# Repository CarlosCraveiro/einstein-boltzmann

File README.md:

# The Einstein-Boltzmann Board

## Project's Intent
Measure the Boltzmann constant through the analysis of the thermal noise of a resistor.

## Disclaimer
This Board was intended to be used with the Guide of the [5-th EPO (2017)](https://github.com/CarlosCraveiro/einstein-boltzmann/tree/main/docs).

So the schematic ideia is not mine, I just adapt and documented it so I could manufacture the board.

The DRC Custom Rules used on this project came from a gist made by [darkxst](https://gist.github.com/darkxst), Gist name: `rules.txt`.

## Project's Dependencies

- KiCAD version 7.0
- KiCAD Addon [kicad-action-scripts](https://github.com/jsreynaud/kicad-action-scripts) (via stitching)

If you use `nix`, to have access to **KiCAD 7.0**, on the project's directory type:

```shell
nix --experimental-features 'nix-command flakes'
nix develop -c $SHELL
```

## Preview Images

### Main Board

### Modules

## Real Photos

## TO DO...
- [ ]  Finish soldering the components and modules
- [ ]  Create a Wiki for the project
- [ ]  Measure the Boltzmann constant and publish the results on the project's Wiki
- [ ]  Finish the plate support base (using FreeCAD)
- [ ]  Write a theoretical introduction about the phenomenon on the project's Wiki

*Observation*: I intend to continue working on the project, I just need time.

## Additional information:

I talked about the project at the [FOSFORUMS 2024](https://www.fosforums.org/home) event. The presentation were in English and both the slides and the link for the presentation recording could be access [here](https://github.com/CarlosCraveiro/FOSFORUMS_2024).

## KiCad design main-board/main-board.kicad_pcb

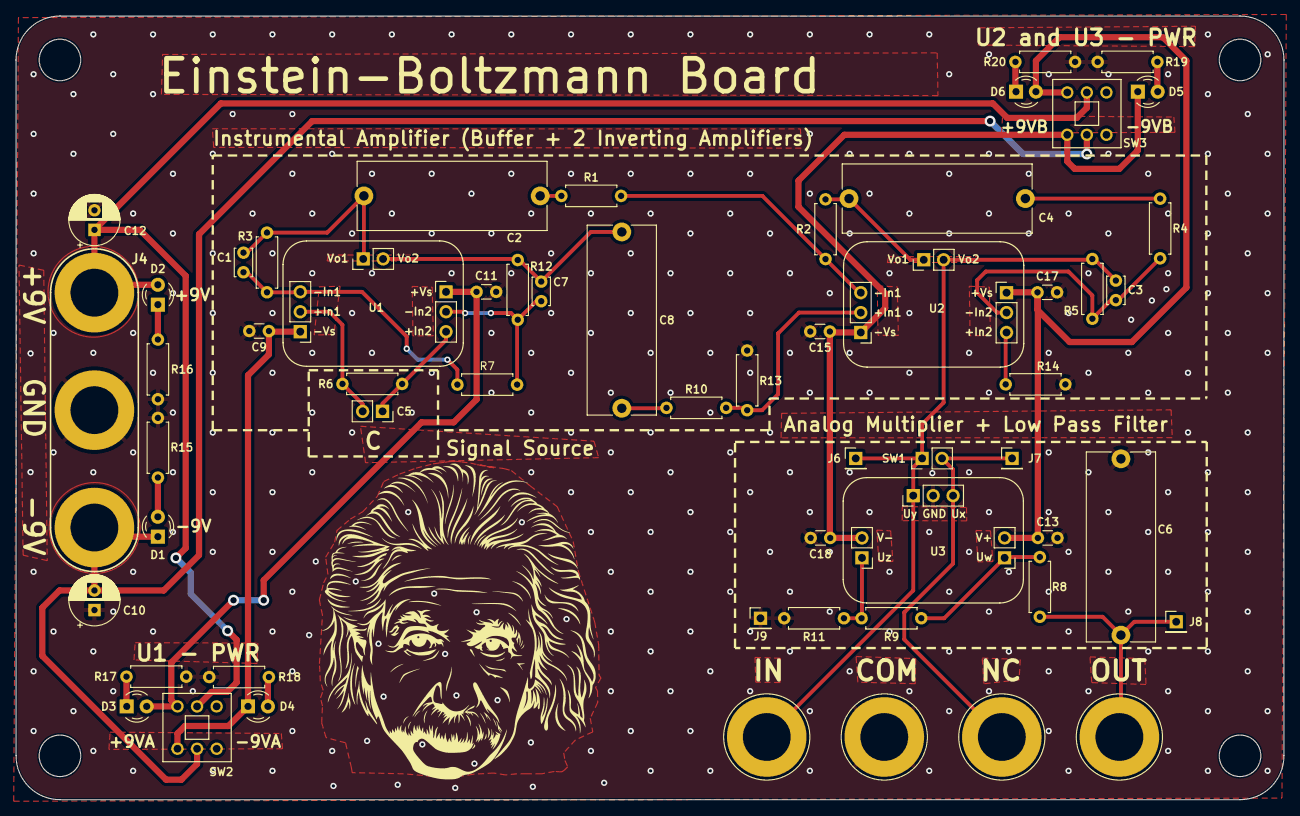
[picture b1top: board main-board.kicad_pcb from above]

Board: 2 copper layers, 161.8 x 100.0 mm, 61 parts (0 on the bottom side), 32 nets.

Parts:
C1, C3, C7: 10p; C_Disc_D3.4mm_W2.1mm_P2.50mm
C2, C4, C6, C8: 10u; C_Rect_L24.0mm_W8.6mm_P22.50mm_MKT
C5: c=?; CapacitorSocket
C9, C11, C13, C15, C17, C18: 0.1u; C_Disc_D3.0mm_W1.6mm_P2.50mm
C10, C12: 10u; CP_Radial_D6.3mm_P2.50mm
D1, D2, D3, D4, D5, D6: LED; LED_D3.0mm
H1, H2, H3, H4: MountingHole; MountingHole_5.3mm_M5
J1: INPUT; Banana_Jack_1Pin
J2: NC1; Banana_Jack_1Pin
J3: OUTPUT; Banana_Jack_1Pin
J4: Conn_01x03_Pin; Banana_Jack_3Pin
J5: COM; Banana_Jack_1Pin
J6: INPUT_DEBUG; PinHeader_1x01_P2.54mm_Vertical
J7: NC__DEBUG; PinHeader_1x01_P2.54mm_Vertical
J8: OUTPUT_DEBUG; PinHeader_1x01_P2.54mm_Vertical
J9: COM_DEBUG; PinHeader_1x01_P2.54mm_Vertical
R1, R4, R10, R14: 100; R_Axial_DIN0207_L6.3mm_D2.5mm_P7.62mm_Horizontal
R2, R5, R13: 10k; R_Axial_DIN0207_L6.3mm_D2.5mm_P7.62mm_Horizontal
R3, R12: 1k; R_Axial_DIN0207_L6.3mm_D2.5mm_P7.62mm_Horizontal
R6: 510; R_Axial_DIN0207_L6.3mm_D2.5mm_P7.62mm_Horizontal
R7: 20; R_Axial_DIN0207_L6.3mm_D2.5mm_P7.62mm_Horizontal
R8: 1.5M; R_Axial_DIN0207_L6.3mm_D2.5mm_P7.62mm_Horizontal
R9, R15, R16, R17, R18, R19, R20: 2k; R_Axial_DIN0207_L6.3mm_D2.5mm_P7.62mm_Horizontal
R11: 18k; R_Axial_DIN0207_L6.3mm_D2.5mm_P7.62mm_Horizontal
SW1: SW_SPST; Switch
SW2: Power Switch A; SW_Push_2P2T_Toggle_CK_PSW-8,0R
SW3: Power Switch B; SW_Push_2P2T_Toggle_CK_PSW-8,0R
U1, U2: ADA4898-2
U3: AD633ANZ; AD633

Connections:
+9V: C12.1, D2.2 (A), J4.1, SW2.2 (B), SW3.2 (B)
+9VA: C11.1, D3.2 (A), SW2.1 (A), U1.6 (+Vs)
+9VB: C13.1, C17.1, D6.2 (A), SW3.1 (A), U2.6 (+Vs), U3.6 (V+)
-9V: C10.2, D1.1 (K), J4.3, SW2.5 (B), SW3.5 (B)
-9VA: C9.1, D4.1 (K), SW2.4 (A), U1.1 (-Vs)
-9VB: C15.1, C18.1, D5.1 (K), SW3.4 (A), U2.1 (-Vs), U3.2 (V-)
/led_+9V: D2.1 (K), R16.1
/led_+9VA: D3.1 (K), R17.1
/led_+9VB: D6.1 (K), R20.1
/led_-9V: D1.2 (A), R15.1
/led_-9VA: D4.2 (A), R18.1
/led_-9VB: D5.2 (A), R19.1
/w1: C1.1, R3.1, R7.1, U1.3 (-In1)
/w2: C7.1, R7.2, R12.2, U1.7 (-In2)
/w3: C1.2, C2.1, R3.2, U1.4 (Vo1)
/w4: C7.2, C8.1, R12.1, U1.5 (Vo2)
/w5: C2.2, R1.1
/w6: C8.2, R10.1
/w7: R1.2, R2.1, U2.3 (-In1)
/w8: R10.2, R13.2, U2.2 (+In1)
/w9: R14.2, U2.8 (+In2)
/w10: C4.1, R2.2, U2.4 (Vo1)
/w11: C4.2, R4.1
/w12: C3.1, R4.2, R5.1, U2.7 (-In2)
/w13: R8.1, R9.1, U3.7 (Uw)
/w14: R9.2, R11.1, U3.1 (Uz)
/w_input: C3.2, J1.1, J6.1, R5.2, SW1.1 (A), U2.5 (Vo2), U3.3 (Uy)
/w_nc: J2.1, J7.1, SW1.2 (B), U3.5 (Ux)
/w_out: C6.1, J3.1, J8.1, R8.2
/w_signal+: C5.2, R6.1, U1.2 (+In1)
/w_signal-: C5.1, R6.2, U1.8 (+In2)
GND: C6.2, C9.2, C10.1, C11.2, C12.2, C13.2, C15.2, C17.2, C18.2, J4.2, J5.1, J9.1, R11.2, R13.1, R14.1, R15.2, R16.2, R17.2, R18.2, R19.2, R20.2, U3.4 (GND)

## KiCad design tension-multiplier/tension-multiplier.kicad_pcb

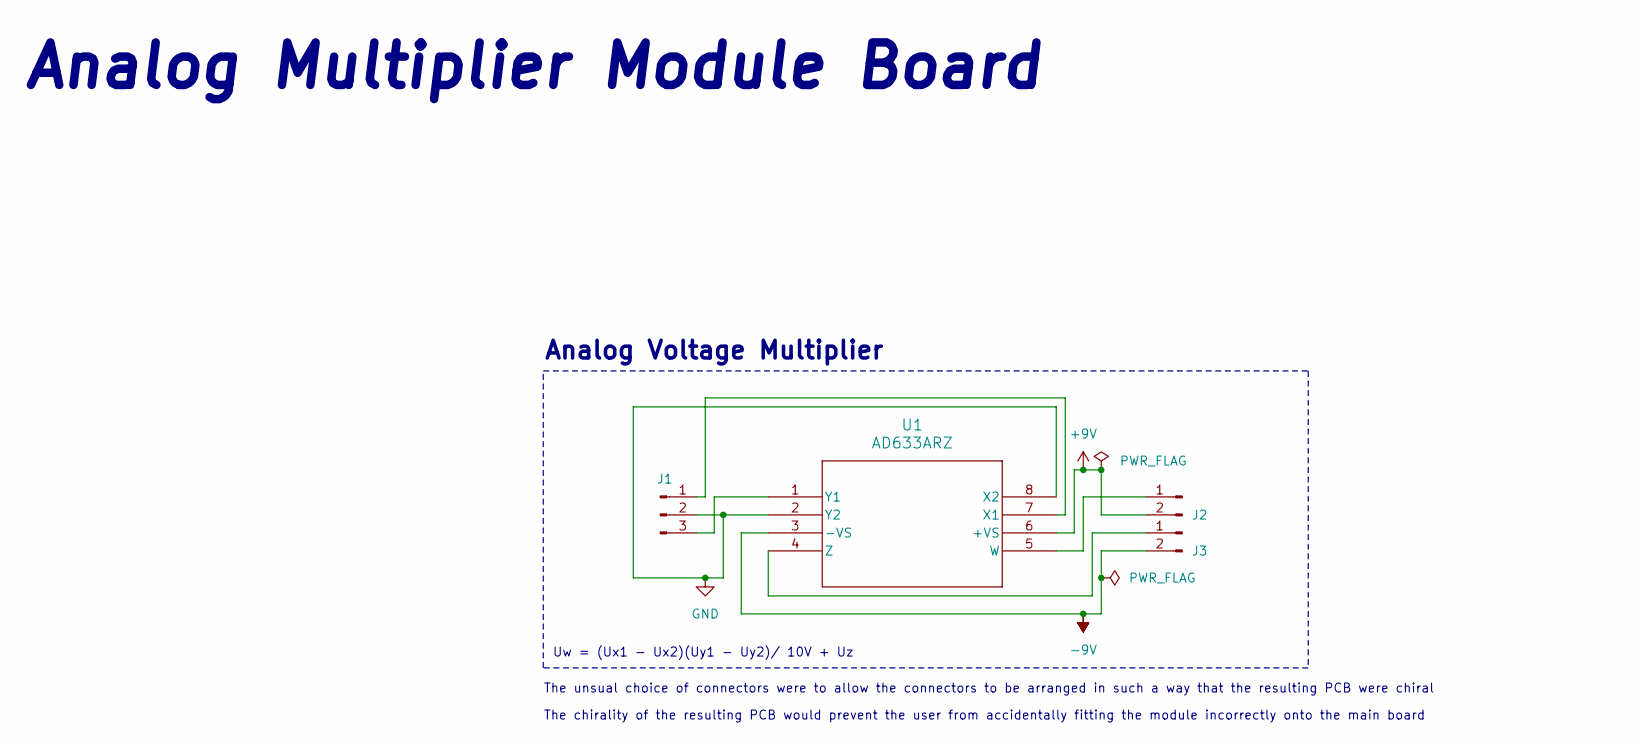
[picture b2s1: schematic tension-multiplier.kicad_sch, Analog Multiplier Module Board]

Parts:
J1: Conn_01x03_Pin; PinHeader_1x03_P2.54mm_Vertical
J2, J3: Conn_01x02_Pin; PinHeader_1x02_P2.54mm_Vertical
U1: AD633ARZ; R_8_ADI

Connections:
+9V: J2.2, U1.6 (+VS)
-9V: J3.2, U1.3 (-VS)
GND: J1.2, U1.2 (Y2), U1.8 (X2)
unnamed: J1.1, U1.7 (X1)
unnamed: J1.3, U1.1 (Y1)
unnamed: J2.1, U1.5 (W)
unnamed: J3.1, U1.4 (Z)

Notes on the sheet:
The chirality of the resulting PCB would prevent the user from accidentally fitting the module incorrectly onto the main board
Analog Multiplier Module Board
Analog Voltage Multiplier
The unsual choice of connectors were to allow the connectors to be arranged in such a way that the resulting PCB were chiral
Uw = (Ux1 - Ux2)(Uy1 - Uy2)/ 10V + Uz

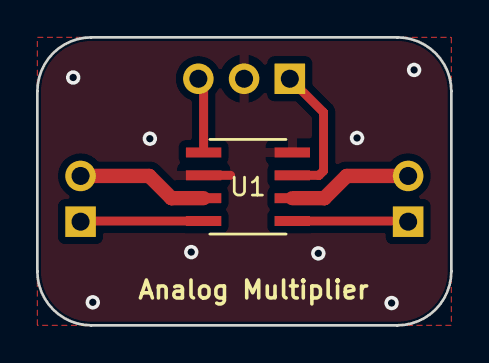
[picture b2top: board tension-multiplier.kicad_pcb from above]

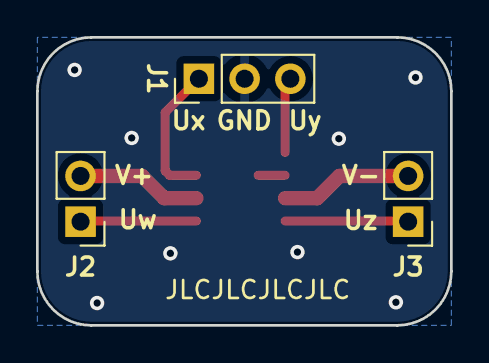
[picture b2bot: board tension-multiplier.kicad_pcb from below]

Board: 2 copper layers, 23.0 x 16.0 mm, 4 parts (3 on the bottom side), 7 nets.

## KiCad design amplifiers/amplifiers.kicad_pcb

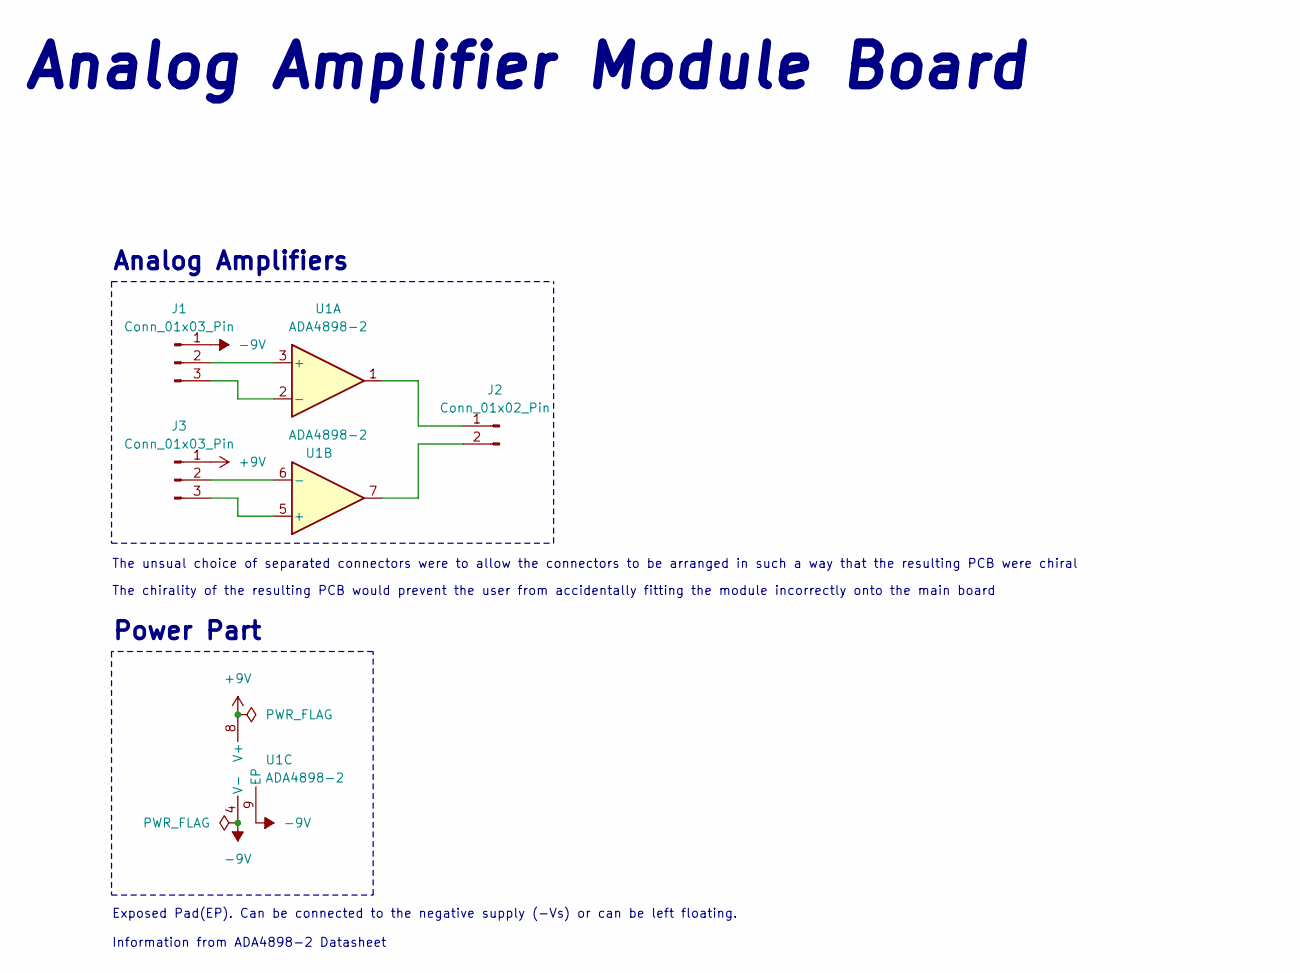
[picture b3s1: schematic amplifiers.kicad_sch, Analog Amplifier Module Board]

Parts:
J1, J3: Conn_01x03_Pin; PinHeader_1x03_P2.54mm_Vertical
J2: Conn_01x02_Pin; PinHeader_1x02_P2.54mm_Vertical
U1: ADA4898-2; SOIC-8-1EP_3.9x4.9mm_P1.27mm_EP2.41x3.81mm

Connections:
+9V: J3.1, U1.8 (V+)
-9V: J1.1, U1.4 (V-), U1.9 (EP)
unnamed: J1.2, U1.3 (+)
unnamed: J1.3, U1.2 (-)
unnamed: J2.1, U1.1
unnamed: J2.2, U1.7
unnamed: J3.2, U1.6 (-)
unnamed: J3.3, U1.5 (+)

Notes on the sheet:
Power Part
The unsual choice of separated connectors were to allow the connectors to be arranged in such a way that the resulting PCB were chiral
Exposed Pad(EP). Can be connected to the negative supply (−Vs) or can be left floating. Information from ADA4898-2 Datasheet
Analog Amplifier Module Board
Analog Amplifiers
The chirality of the resulting PCB would prevent the user from accidentally fitting the module incorrectly onto the main board

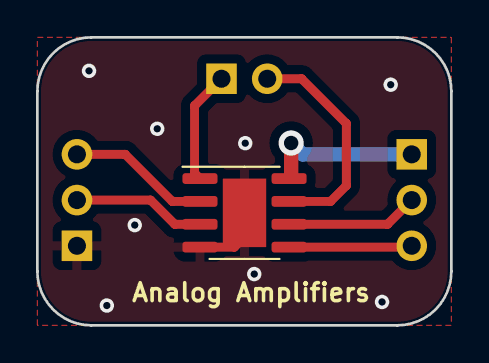
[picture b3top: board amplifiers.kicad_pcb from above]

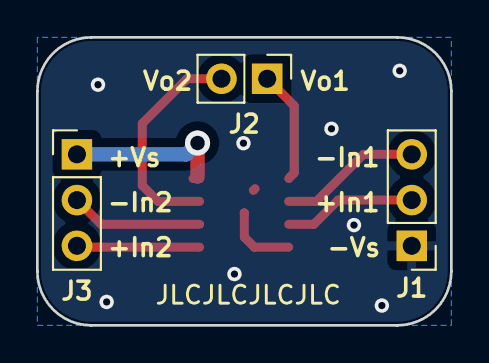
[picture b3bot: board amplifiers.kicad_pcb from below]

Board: 2 copper layers, 23.0 x 16.0 mm, 4 parts (3 on the bottom side), 8 nets.

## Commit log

2024-02-06 Creates a .gitignore
2024-02-06 creates main board project
2024-02-06 creates amplifiers project
2024-02-06 creates tension-multiplier project
2024-02-06 adds *.kicad_sch.lck files to ignore list
2024-02-06 Updates .gitignore
2024-02-06 Finishes version 0.1 of the analog multiplier schematic
2024-02-06 Adds CERN-OHL-S (strongly reciprocal)v2 LICENSE
2024-02-06 Starts PCB layout for analog multiplier
2024-02-07 Finishes version 0.1 of Analog Multiplier Module
2024-02-07 start design of Amplifier module boards
2024-02-07 Finishes version 0.1 of amplifier module board
2024-02-08 Starts the Main Board design
2024-02-11 Adds a working Simulation
2024-02-11 Adds some flootprints to the main board
2024-02-12 Selects all footprints to the main board schematics
2024-02-13 Adjust main board footprints and pcb layout
2024-02-13 Modifies PCB Layout cosmetics
2024-02-13 Changes dimentions of the tension multiplier
2024-02-14 Refactors modules pcblayout to cosmetic purposes
    Also, refactors Amplifiers moduleboard to include a VEE plane
    (powerplane).
2024-02-14 Changes 3d files and footprints to match module cosmetic changes
2024-02-14 Modifies Main Board PCB Layout component disposal
2024-02-14 Modifies main board layout components displacement
2024-02-14 Starts routing the main board
2024-02-15 Finishes version Beta of the project
2024-02-15 Starts Pannelization
2024-02-16 test gerber files and add JLC serial number to the main board
2024-02-16 Starts the Bill of Materials of the project
2024-02-16 Add JLCPCB serial number to the module pcbs
2024-02-16 Give up from the idea from pannelization
2024-02-16 Updates BOM
2024-02-17 Add Capacitor Prices
2024-02-17 Add LED price
2024-02-17 Add resistor prices
2024-02-17 Add mini-jumper price
2024-02-17 add capacitor price incomplete
2024-02-17 Adds capacitor and pin headers and socket prices
2024-02-21 Starts design of mounting base
2024-02-21 Change M8 Holes to M5 Holes
2024-07-08 Adds flake to lock Kicad version on version 7
2024-08-04 Adds a TODO List and a flake.lock
2024-08-04 Changes capacitor and resistor footprints
2024-08-05 Saves progress
2024-08-06 Adds Switch footprint and 3d model
2024-08-06 Solves the 4 batteries problem
2024-08-09 Save changes
2024-08-11 Improves components displacement
2024-08-11 Updates TODO List
2024-08-15 Continues placement process
2024-08-15 Finishes Component displacement
2024-08-15 Done Routing with DRC 0 Errors and 0 Warnings
2024-08-15 Adds upper ground plane and via stitches the board
2024-08-16 Adds design rules to amplifiers and tension multiplier folders
2024-08-16 Modifies auxiliary boards
2024-08-16 Finishes the main board
2024-08-16 Adds the fabrication zip files submited to JLC PCB
2024-08-16 Adds new tasks on the TODO List
2024-08-17 Adds the orginal paper on which the board was based
2024-08-17 add images of the main board
2024-08-22 Changes the version from 0.1 to 1.0
2024-08-22 Credits the DRC custom rules
2024-08-22 adds project images
2024-08-25 modifies the images
2024-08-25 Adds real photos of the board
